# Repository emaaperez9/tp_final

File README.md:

# tp_final
Primer Carpeta Tp Final

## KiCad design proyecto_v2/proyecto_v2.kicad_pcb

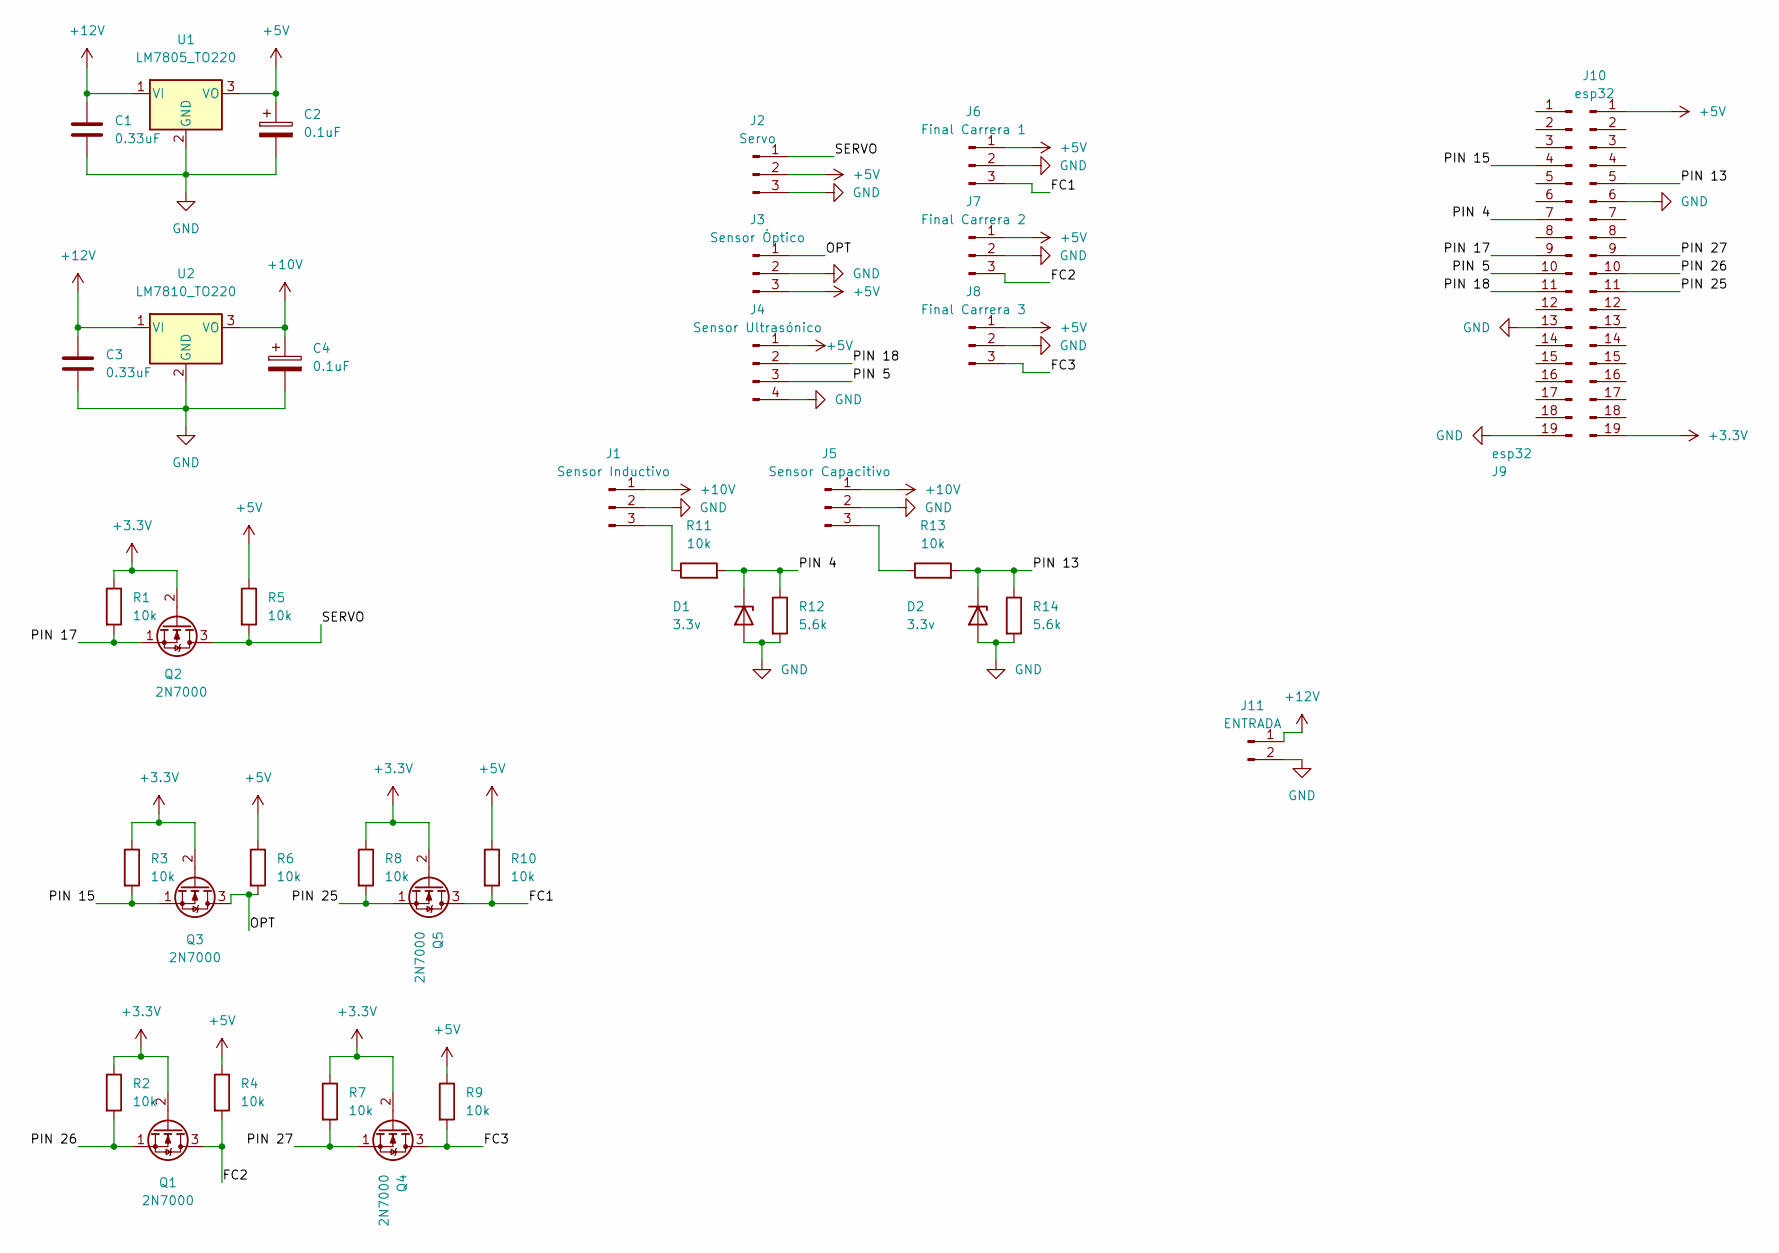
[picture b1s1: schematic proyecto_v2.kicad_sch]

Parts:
C1, C3: 0.33uF; C_Disc_D3.0mm_W2.0mm_P2.50mm
C2, C4: 0.1uF; C_Disc_D3.0mm_W2.0mm_P2.50mm
D1, D2: 3.3v; D_A-405_P2.54mm_Vertical_AnodeUp
J1: Sensor Inductivo; PinHeader_1x03_P1.00mm_Vertical
J2: Servo; PinHeader_1x03_P1.00mm_Vertical
J3: Sensor Óptico; PinHeader_1x03_P1.00mm_Vertical
J4: Sensor Ultrasónico; PinHeader_1x04_P1.00mm_Vertical
J5: Sensor Capacitivo; PinHeader_1x03_P1.00mm_Vertical
J6: Final Carrera 1; PinHeader_1x03_P1.00mm_Vertical
J7: Final Carrera 2; PinHeader_1x03_P1.00mm_Vertical
J8: Final Carrera 3; PinHeader_1x03_P1.00mm_Vertical
J9, J10: esp32; PinHeader_1x19_P1.00mm_Vertical
J11: ENTRADA; PinSocket_1x02_P1.00mm_Vertical
Q1, Q2, Q3, Q4, Q5: 2N7000; TO-92_Inline
R1, R2, R3, R4, R5, R6, R7, R8, R9, R10, R11, R13: 10k; R_Axial_DIN0207_L6.3mm_D2.5mm_P7.62mm_Horizontal
R12, R14: 5.6k; R_Axial_DIN0207_L6.3mm_D2.5mm_P7.62mm_Horizontal
U1: LM7805_TO220; TO-220-3_Vertical
U2: LM7810_TO220; TO-220-3_Vertical

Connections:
+3.3V: J10.19, Q1.2 (G), Q2.2 (G), Q3.2 (G), Q4.2 (G), Q5.2 (G), R1.1, R2.1, R3.1, R7.1, R8.1
+5V: C2.1, J2.2, J3.3, J4.1, J6.1, J7.1, J8.1, J10.1, R4.1, R5.1, R6.1, R9.1, R10.1, U1.3 (VO)
+10V: C4.1, J1.1, J5.1, U2.3 (VO)
+12V: C1.1, C3.1, J11.1, U1.1 (VI), U2.1 (VI)
/FC1: J6.3, Q5.3 (D), R10.2
/FC2: J7.3, Q1.3 (D), R4.2
/FC3: J8.3, Q4.3 (D), R9.2
/OPT: J3.1, Q3.3 (D), R6.2
/PIN 4: D1.1 (K), J9.7, R11.2, R12.1
/PIN 5: J4.3, J9.10
/PIN 13: D2.1 (K), J10.5, R13.2, R14.1
/PIN 15: J9.4, Q3.1 (S), R3.2
/PIN 17: J9.9, Q2.1 (S), R1.2
/PIN 18: J4.2, J9.11
/PIN 25: J10.11, Q5.1 (S), R8.2
/PIN 26: J10.10, Q1.1 (S), R2.2
/PIN 27: J10.9, Q4.1 (S), R7.2
/SERVO: J2.1, Q2.3 (D), R5.2
GND: C1.2, C2.2, C3.2, C4.2, D1.2 (A), D2.2 (A), J1.2, J2.3, J3.2, J4.4, J5.2, J6.2, J7.2, J8.2, J9.13, J9.19, J10.6, J11.2, R12.2, R14.2, U1.2 (GND), U2.2 (GND)
unnamed: J1.3, R11.1
unnamed: J5.3, R13.1

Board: 2 copper layers, 38 parts (0 on the bottom side), 21 nets, no tracks yet.

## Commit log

2022-07-27 Creo_Proyecto
2022-07-27 Create Nuevo Documento de Microsoft Word.docx
    Agrego word
2022-07-27 Update tp_final.ino
    agregue un comentario
2022-07-28 Update tp_final.ino
    cambiolinea5
2022-07-28 sda
    asd
2022-08-18 pruebaservo
2023-01-11 cambiopines
2023-03-21 schematic
